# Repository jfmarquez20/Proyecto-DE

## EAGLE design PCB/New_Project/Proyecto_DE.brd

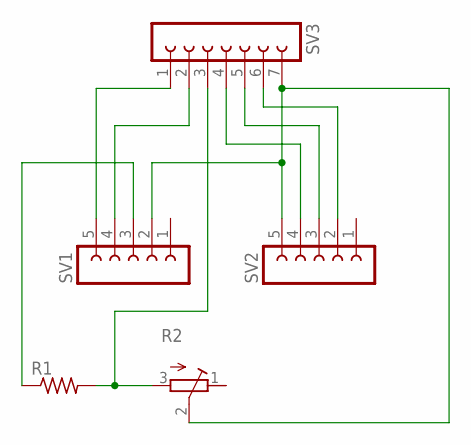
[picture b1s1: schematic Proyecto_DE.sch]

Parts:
R1: R-US_0207/12; 0207/12
R2: R-TRIMMT93YA; RTRIMT93YA
SV1, SV2: FE05-1
SV3: FE07-1; FE07

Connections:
unnamed: SV1.5, SV3.1
unnamed: SV1.4, SV3.2
unnamed: R1.1, SV1.3
unnamed: R1.2, R2.3 (A), SV3.3
unnamed: SV2.4, SV3.4
unnamed: SV2.3, SV3.5
unnamed: R2.2 (S), SV1.2, SV2.5, SV3.7
unnamed: SV2.2, SV3.6

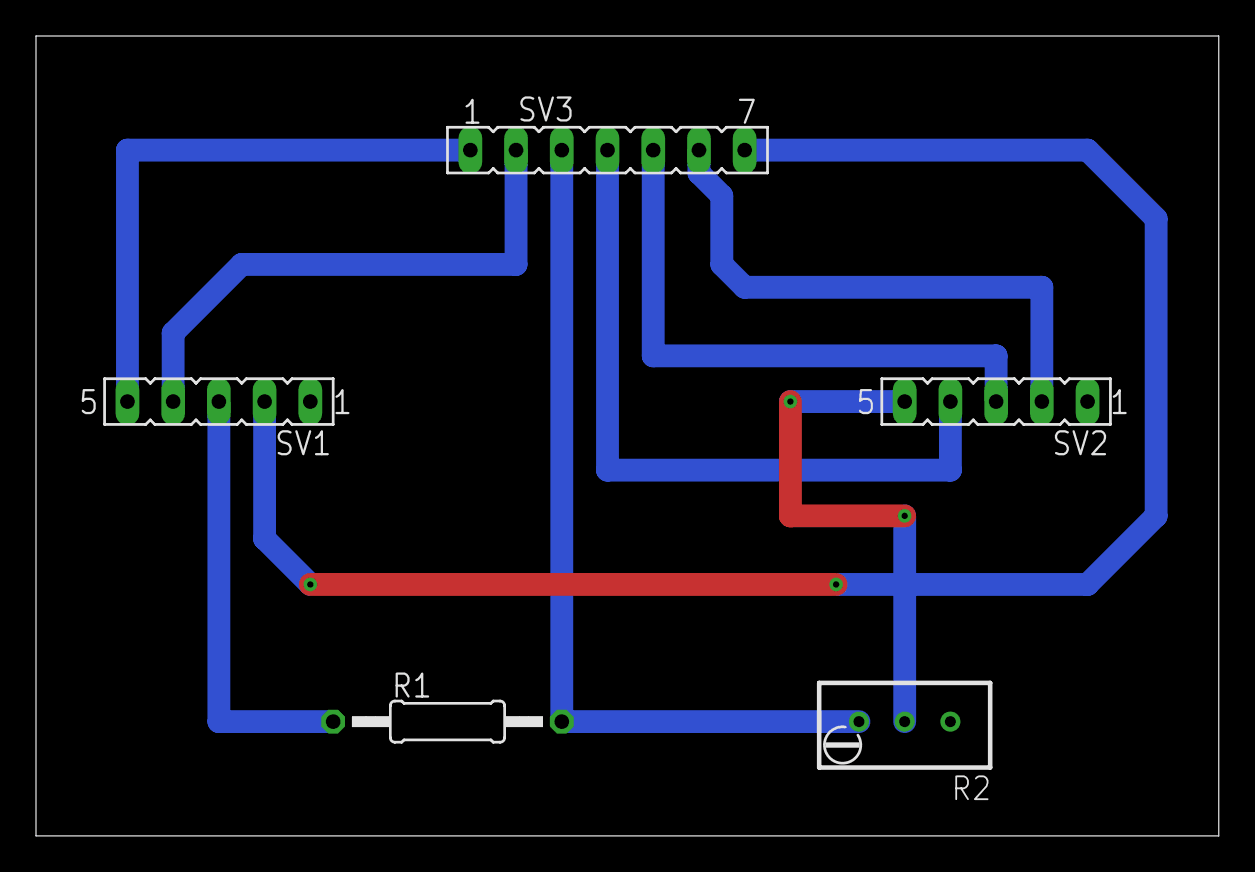
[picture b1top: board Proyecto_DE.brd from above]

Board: 2 copper layers, 65.7 x 44.4 mm, 5 parts (0 on the bottom side), 8 nets.

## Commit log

2020-08-26 Send data through TCP and UDP
2020-08-26 SMS and GPS working
2020-09-02 TCP and UDP
2020-09-08 No broadcast TCP and UDP
2020-09-08 Primera versión del web server
2020-09-08 NO BROADCAST + REPEATED SENDING
2020-09-08 UI changed
2020-09-08 test
2020-09-08 WebServer working - no dynamically
2020-09-08 WebServer working dynamically FIXED
2020-09-08 fix: Port 15002
2020-09-09 Remote WebServer
2020-09-09 QoS changes to WebServer (nodemon)
2020-09-09 Updated UI, added stop button.
2020-09-11 feat: Backend with Express, API Google Maps, CSS
2020-09-12 Error CSS file
2020-09-14 feat: API Maps update marker dynamically
2020-09-15 Some changes on front
2020-09-16 MySQL with node.js training
2020-09-16 Local database added
2020-09-18 Drawing routes with Polylines
2020-09-18 FIXED IPs and DATETIME format
2020-09-20 Functional DB on RDS + Command to connect on SSH
2020-09-23 New Elastic IPs
2020-09-23 DB Password Security
2020-09-23 minor changes to env.txt
2020-09-23 fix: Map center
2020-09-27 feat: No buttons on index and CSS file working
2020-09-28 Historical form with JQuery and handling POST requests
2020-09-28 Tracing routes with historical data
2020-09-30 Functional API
2020-09-30 fix: onLoad Map and Modal text
2020-10-03 fix: Reset polyline and new features with Datetimepicker
2020-10-03 fix: .env file
2020-10-05 feat: Alert when data is not found in DB
2020-10-06 fix: New API Google Maps
2020-10-12 User experience - Snapped-to-roads line
2020-10-13 Snap to ROADS in Live-time tracker update
2020-10-13 Script changes
2020-10-13 html script edits
2020-10-13 Live road snapping
2020-10-14 Enviroment socket variable
2020-10-14 fix: Waiting to localhost and change POST Route
2020-10-20 findByPlace + minor changes
2020-10-21 FindByPlace function with no delete of previous markers
2020-10-21 APP: added truck ID
2020-10-21 fix: Remove previous markers and add second truck
2020-10-21 feat: var Color polylines
2020-10-21 fix: Minor changes on infoWindow
2020-10-22 fix: Inputs readonly disabled and close previous infoWindow
2020-10-24 fix: findByPlace based on historical search
2020-10-24 Lil change on findByPlace
2020-10-28 Tracker selector on index
2020-10-28 fix: RadioButtons and generate circle
2020-10-28 Adicion de variable cambiante
2020-10-28 Some changes
2020-10-28 FUNCT API
2020-11-04 Polyline selection
2020-11-07 BT Socket
2020-11-11 Final Bt
2020-11-11 Some changes for UX
2020-11-11 PCB Design with Eagle
